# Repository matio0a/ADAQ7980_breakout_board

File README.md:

# ADAQ7980_breakout_board
A KiCad project of a breakout board design for ADAQ7980 - 16-bit 1 MSPS Analog-to-Digital converter.
The project contains the necessary symbols and footprints, as well as the schematics and PCB layout of a breakout board that can be used for rapid prototyping with ADAQ7980. 

**Board description:**

  - ADAQ7980 pins are accessible through the external pin headers.
  - The IN+ pin is additionally accessible through the on-board SMA-connector. The input pin is 50 Ohm-terminated.
  - A 4.096 V precision voltage reference (ADR4540) is used to fix the ADC range.
  - The input amplifier is configured as a unity-gain buffer. Footprints for gain-setting resistors as well as for a feedbac capacitor are present. The unity-gain setting is achieved by soldering a 0-Ohm SMD resistor instead of R2.
  - A 47k resistor is soldered between VIO and SDO pins to create an additional "Busy" signal on the SDO line. This feature can be turned off by tying the SDO line to VIO directly.
  - A green LED is present to indicate the power on condition.
  - SDI line is accessible through the dedicated pin header. Place a jumper between SDI and VIO to operate in a 3-wire SPI mode.
  - V- line is accessible through the dedicaed pin header. Place a jumper between V- and GND pins to operate in a single-supply mode.

**To do:**

  - Redo the board layout.
  - Create production files.

Licensed under CERN-OHL-P v2.

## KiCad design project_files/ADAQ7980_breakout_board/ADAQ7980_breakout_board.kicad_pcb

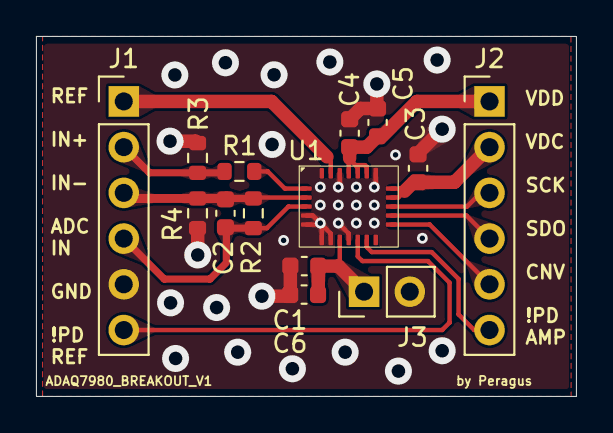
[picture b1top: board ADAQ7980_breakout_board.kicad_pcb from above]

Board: 2 copper layers, 30.0 x 20.0 mm, 14 parts (0 on the bottom side), 14 nets.

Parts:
C1, C3, C4: 100n; C_0603_1608Metric
C2: 8p; C_0603_1608Metric
C5, C6: 2.2u; C_0603_1608Metric
J1, J2: Conn_01x06; PinHeader_1x06_P2.54mm_Vertical
J3: Conn_01x02; PinHeader_1x02_P2.54mm_Vertical
R1, R2, R3, R4: R_0603_1608Metric
U1: ADAQ7980

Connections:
/!PD_AMP: J2.6, U1.11 (!PD_AMP)
/!PD_REF: J1.6, U1.10 (!PD_REF)
/AMP_OUT/ADC_IN: C2.2, J1.4, R2.2, U1.3 (AMP_OUT)
/CNV: J2.5, U1.13 (CNV)
/IN+: J1.2, R1.1, R3.2
/IN-: C2.1, J1.3, R2.1, R4.2, U1.2 (In-)
/OUT+: R1.2, U1.1 (In+)
/REF: J1.1, U1.23 (REF)
/SCK: J2.3, U1.15 (CSK)
/SDO: J2.4, U1.14 (SDO)
GND: C1.2, C3.2, C4.2, C5.2, C6.2, J1.5, J3.2, R3.1, R4.1, U1.4 (ADCN), U1.5 (GND), U1.6 (GND), U1.7 (GND), U1.9 (GND), U1.18 (GND), U1.22 (GND)
VDC: C3.1, J2.2, U1.16 (SDI), U1.17 (VIO)
VDD: C4.1, C5.1, J2.1, U1.19 (!PD_LDO), U1.20 (VDD), U1.21 (V+)
VSS: C1.1, C6.1, J3.1, U1.8 (V-)

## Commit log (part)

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2026-06-28 Add CERN Open Hardware Licence Version 2 - Permissive
    This file contains the CERN Open Hardware Licence Version 2 - Permissive, detailing terms for use, modification, and distribution of hardware designs.
2026-06-28 Enhance README with detailed project description
    Expanded project description with details on design features and usage.
2026-06-28 Added source files for the libraries as well as the ADC datasheet.
